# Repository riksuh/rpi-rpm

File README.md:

# Raspberry Pi Remote Power Management
Mini-server run on a Raspberry Pi to control my home server using GPIO pins connected to the motherboard's system panel connector (with a few resistors and opto-couplers inbetween of course)

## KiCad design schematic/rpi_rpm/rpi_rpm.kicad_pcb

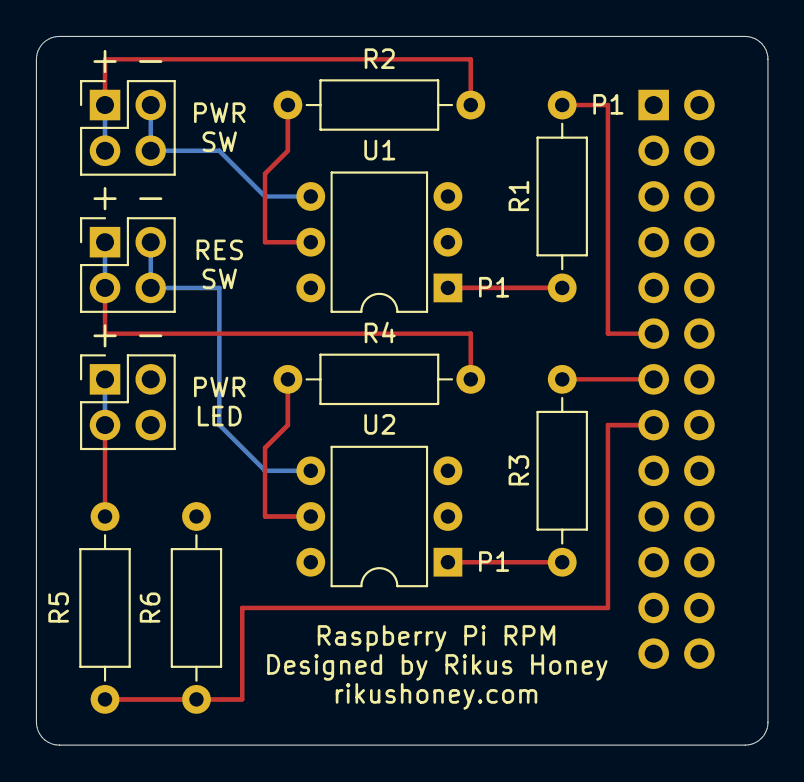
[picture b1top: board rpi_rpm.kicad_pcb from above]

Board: 2 copper layers, 40.6 x 39.4 mm, 12 parts (1 on the bottom side), 13 nets.

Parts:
J1: Raspberry Pi Pins; PinSocket_2x13_P2.54mm_Vertical
J2: PWR_SW; PinHeader_2x02_P2.54mm_Vertical
J3: RES_SW; PinHeader_2x02_P2.54mm_Vertical
J4: PWR_LED; PinHeader_2x02_P2.54mm_Vertical
R1, R3: 220R; R_Axial_DIN0207_L6.3mm_D2.5mm_P10.16mm_Horizontal
R2, R4: 100R; R_Axial_DIN0207_L6.3mm_D2.5mm_P10.16mm_Horizontal
R5: 18k; R_Axial_DIN0207_L6.3mm_D2.5mm_P10.16mm_Horizontal
R6: 33k; R_Axial_DIN0207_L6.3mm_D2.5mm_P10.16mm_Horizontal
U1, U2: 4N35; DIP-6_W7.62mm

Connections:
GND: J1.9, J4.2, J4.4, R6.1, U1.2, U2.2
unnamed: J2.1, J2.3, R2.1
unnamed: J2.2, J2.4, U1.4
unnamed: J3.1, J3.3, R4.1
unnamed: J3.2, J3.4, U2.4
unnamed: J4.1, J4.3, R5.1
unnamed: R1.1, U1.1
unnamed: R2.2, U1.5
unnamed: R3.1, U2.1
unnamed: R4.2, U2.5
PWR_LED: J1.15, R5.2, R6.2
PWR_SW: J1.11, R1.2
RES_SW: J1.13, R3.2

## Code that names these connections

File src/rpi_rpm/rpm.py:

from .server import BaseServer

import json
from typing import Dict

from gpiozero import DigitalInputDevice, DigitalOutputDevice
from werkzeug.wrappers import Response
from werkzeug.utils import redirect


class RemotePowerModule(BaseServer):
    def __init__(self, pwr_pin, res_pin, led_pin):
        super().__init__()
        self._pwr_sw = DigitalOutputDevice(pwr_pin)
        self._res_sw = DigitalOutputDevice(res_pin)
        self._pwr_led = DigitalInputDevice(led_pin)

    @property
    def power_status(self) -> Dict:
        return {
            "power": "on" if self._pwr_led.value == 1 else "off"
        }

    def power_on(self):
        if self.power_status["power"] == "off":
            self._pwr_sw.blink(on_time=0.5, n=1)

    def power_off(self):
        if self.power_status["power"] == "on":
            self._pwr_sw.blink(on_time=0.5, n=1)

    def reset(self):
        self._res_sw.blink(on_time=0.5, n=1)


def make_json_response(data: Dict) -> Response:
    return Response(json.dumps(data), mimetype="application/json")


def create_rpm_server(pwr_pin=17, res_pin=27, led_pin=22) -> BaseServer:
    server = RemotePowerModule(pwr_pin, res_pin, led_pin)

    @server.route("/")
    @server.route("/status")
    def status():
        return make_json_response(server.power_status)

    @server.route("/power-on")
    def power_on():
        server.power_on()
        return redirect("/")

    @server.route("/power-off")
    def power_off():
        server.power_off()
        return redirect("/")

    @server.route("/reset")
    def reset():
        server.reset()
        return redirect("/")

    return server

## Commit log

2019-10-21 Base server
2019-10-21 Added command-line interface with setuptools
2019-10-21 Spotted bug when port not specified
2019-10-22 Better help
2019-10-22 Created schematic for add-on board
2019-10-25 Updated schematic for jumper pins
2019-10-26 Organized server and added power management routes
2019-10-26 Forgot to call base constructor
2019-10-26 Updated version and added redirects
2019-11-25 Added schematic pdf
